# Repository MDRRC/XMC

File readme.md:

# Xpressnet Manual Control

The XpressNet Manual Control (Xmc) is manual control for the [XPressnet bus](www.lenzusa.com/1newsite1/Manuals/xpressnet.pdf) based on 

 * An [Maple Mini STM32 board](https://www.leaflabs.com/maple/) variant from China with **128K flash** memory and not the 64K variant!
 * RS485 driver IC
 * AT24C256 memory IC for storage of settings and locomotive data.
 * 128*128 pixel ST7735 LCD. When ordering a display make sure the pinning is the same as shown in image below
 * Push buttons for controlling functions / accesory decoders / menu related actions. 
 * Pulse switch for setting speed / menu related actions.
 
The user interface is nearly the same as with the WMC application and it's tried to reuse / update library's created for WMC.

## Tested with
 * [MDRRC-II](http://members.home.nl/robert.evers/mdrrc2.htm) Response ok. 
 * [Roco MultiMaus as master](https://www.roco.cc/en/product/5215-multimaus-0-0-0-0-0-004001-0/products.html) OK for locs, turnouts not tested yet.

## Schematic
The [schematic](https://github.com/MDRRC/XMC/blob/master/Doc/xmc_schematic.pdf) of the XMC.

## PCB front and back side.
The PCB from the front and back. 

## Programming the STM32 
The STM32 can be programmed without the need to build the software. By using a programming tool from the STM32 Arduino library the STM32 can be programmed with the buildin bootloader of the STM32 on the USB connection.
 * The [Stm32 Arduino library](https://github.com/rogerclarkmelbourne/Arduino_STM32) must be present on your PC.
 * Open the DOS box and enter command below (Location of files on your own PC might differ and the COM port will probably also be different, so change it accordingly!!)
 > C:/Arduino_STM32-master/tools/win/maple_upload.bat COM9 1 1EAF:0003 C:/LocationOfBinFileOnYourPc/Xmc.bin
 * The bin file is flashed into the STM32.
 * When ready, the screen stays gray for ~3 seconds and subsequent the start screen appears.
 
## Programming the STM32 with FLASHER-STM32
The STM32 can also be programmed with [Flasher-STM32](https://www.st.com/en/development-tools/flasher-stm32.html)
 * Connect an USB serial to TTL level (!) adapter to RX1 and TX1 (pin 25 and 26). The USB connector can NOT be used in this case for programmming!!! 
 * Connect the BOOT1 pin to ground when programming the STM32 out out the XMC PCB. 
 * Connect an USB cable to the USB connector of the STM32 module so it has supply voltage when programming the STM32 out out the XMC PCB. 
 * Follow instructions of chapter 5. Software update of [MDRRC-II Lite](https://github.com/MDRRC/Doc/blob/master/mdrrc_ii_lite.zip)
 * Select the XmcComplete.bin and flash the file. The bin file is WITH bootloader! 
 * When ready press RESet button, the screen stays gray for ~3 seconds and subsequent the start screen appears.   
 
## Used library's
If you want to build the code yourself or update / change the code following library's are required.
 * [XmcApp](https://github.com/MDRRC/XmcApp) the main state machine of the application.
 * [TinyFsm](https://github.com/digint/tinyfsm) for state machine framework.
 * [XpressNet](https://github.com/MDRRC/XpressNet) for XpressNet protocol.
 * [Bounce2](https://github.com/thomasfredericks/Bounce2) for debouncing switches.
Bounce requires an update for use in the XMC application, add the include and replace the attach function with code below
```c
#include "app_cfg.h"
 
void Bounce::attach(int pin, int mode)
{
  #ifdef MCU_STM32F103RB
  pinMode(pin, (WiringPinMode)(mode));
  #else
  pinMode(pin, mode);
  #endif
  this->attach(pin);
}
```
 * [Adafruit-ST7735-Library](https://github.com/adafruit/Adafruit-ST7735-Library) to control the display.
 * [WmcTft](https://github.com/MDRRC/WmcTft) for graphics within the XMC application.
 * [Adafruit-GFX-Library](https://github.com/adafruit/Adafruit-GFX-Library) for graphic control of the display.
 * [LocLib](https://github.com/MDRRC/LocLib) for handling locomotive data within the XMC application.
 * [WmcCv](https://github.com/MDRRC/WmcCv) for changing CV's.
 * [WmcCli](https://github.com/MDRRC/WmcCli) for the command line interface over the USB serial port.
 * [Stm32 Arduino library](https://github.com/rogerclarkmelbourne/Arduino_STM32), use the [1.0.0 release](https://github.com/rogerclarkmelbourne/Arduino_STM32/releases/tag/v1.0.0)! The most recent version at the master may give problems because of some changes.  
 
 In the Stm32 Arduino library
 * Remove or rename (.x for example) ..\Arduino_STM32-master\STM32F1\cores\maple\libmaple\usart.c so it's NOT build
 * Remove or rename (.x for example) ..\Arduino_STM32-master\STM32F1\cores\maple\libmaple\usart_f1.c so it's NOT build 
 * Remove or rename (.x for example) ..\Arduino_STM32-master\STM32F1\system\libmaple\usart_private.h so it's NOT build 
 
 The three files are in [XpressNet](https://github.com/MDRRC/XpressNet) and are required for correct handling of 9 bit communication handling.

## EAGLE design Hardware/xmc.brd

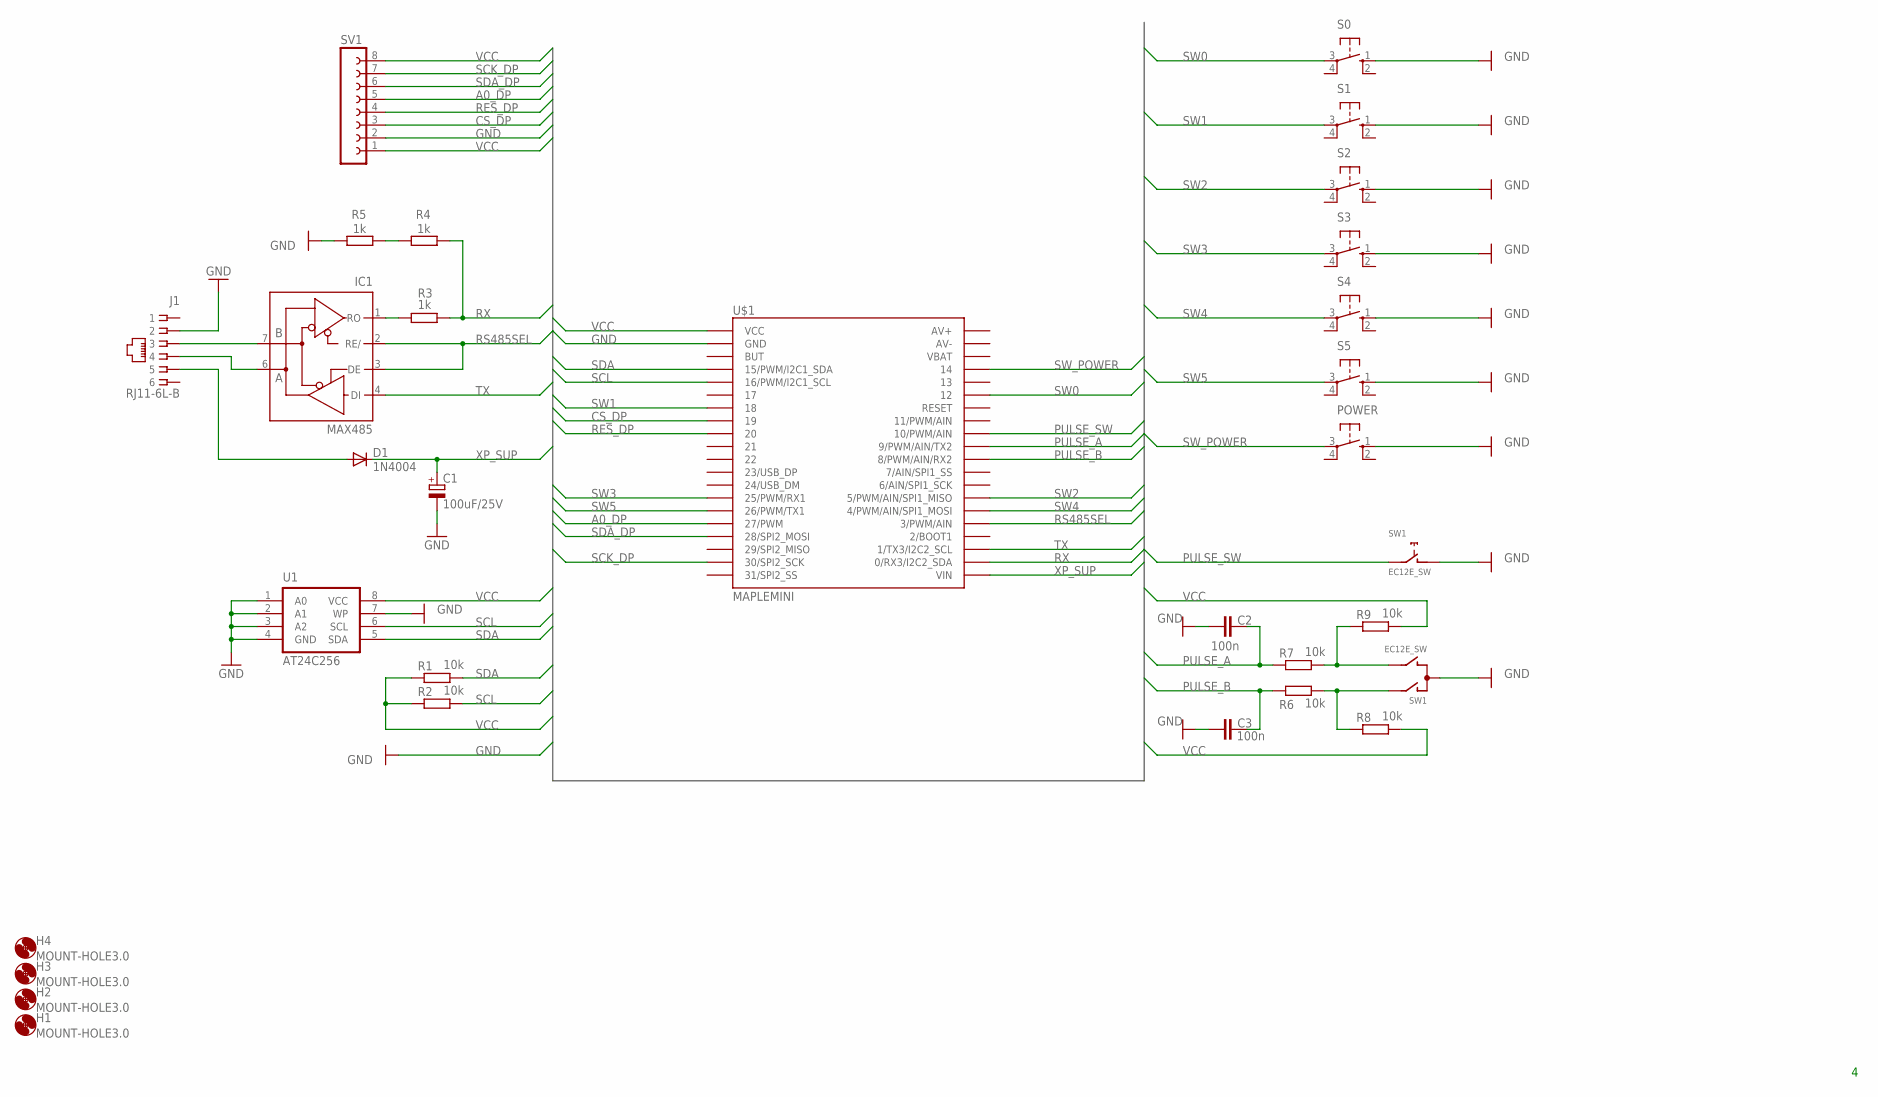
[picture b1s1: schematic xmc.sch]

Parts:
C1: 100uF/25V; E2,5-6
C2, C3: 100n; C025-024X044
D1: 1N4004; DO41-10
H1, H2, H3, H4: MOUNT-HOLE3.0; 3,0
IC1: MAX485; SO08
J1: RJ11-6L-B; RJ11-NO_SHIELD
POWER: 10-XX; B3F-10XX
R1, R2, R6, R7, R8, R9: 10k; 0207/7
R3, R4, R5: 1k; 0207/7
S0, S1, S2, S3, S4, S5: 10-XX; B3F-10XX
SV1: FE08-1; FE08
SW1: EC12E_SW; ALPS_EC12E_SW
U1: AT24C256; SO08-8S1
U$1: MAPLEMINI; 20-DIP

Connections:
A0_DP: SV1.5, U$1.16 (27/PWM)
CS_DP: SV1.3, U$1.8 (19)
GND: C1.-, C2.2, C3.2, IC1.5 (GND), J1.2, POWER.1 (S), R5.2, S0.1 (S), S1.1 (S), S2.1 (S), S3.1 (S), S4.1 (S), S5.1 (S), SV1.2, SW1.C, SW1.D (1), U1.1 (A0), U1.2 (A1), U1.3 (A2), U1.4 (GND), U1.7 (WP), U$1.2 (GND)
unnamed: R7.2, R9.1, SW1.B
unnamed: R6.2, R8.1, SW1.A
unnamed: D1.A, J1.5
unnamed: IC1.1 (RO), R3.1
unnamed: R4.2, R5.1
unnamed: IC1.7 (B), J1.3
unnamed: IC1.6 (A), J1.4
PULSE_A: C2.1, R7.1, U$1.31 (9/PWM/AIN/TX2)
PULSE_B: C3.1, R6.1, U$1.30 (8/PWM/AIN/RX2)
PULSE_SW: SW1.E (2), U$1.32 (10/PWM/AIN)
RES_DP: SV1.4, U$1.9 (20)
RS485SEL: IC1.2 (RE/), IC1.3 (DE), U$1.25 (3/PWM/AIN)
RX: R3.2, R4.1, U$1.22 (0/RX3/I2C2_SDA)
SCK_DP: SV1.7, U$1.19 (30/SPI2_SCK)
SCL: R2.2, U1.6 (SCL), U$1.5 (16/PWM/I2C1_SCL)
SDA: R1.2, U1.5 (SDA), U$1.4 (15/PWM/I2C1_SDA)
SDA_DP: SV1.6, U$1.17 (28/SPI2_MOSI)
SW0: S0.3, U$1.35 (12)
SW1: S1.3, U$1.7 (18)
SW2: S2.3, U$1.27 (5/PWM/AIN/SPI1_MISO)
SW3: S3.3, U$1.14 (25/PWM/RX1)
SW4: S4.3, U$1.26 (4/PWM/AIN/SPI1_MOSI)
SW5: S5.3, U$1.15 (26/PWM/TX1)
SW_POWER: POWER.3, U$1.37 (14)
TX: IC1.4 (DI), U$1.23 (1/TX3/I2C2_SCL)
VCC: IC1.8 (VCC), R1.1, R2.1, R8.2, R9.2, SV1.1, SV1.8, U1.8 (VCC), U$1.1 (VCC)
XP_SUP: C1.+, D1.C, U$1.21 (VIN)

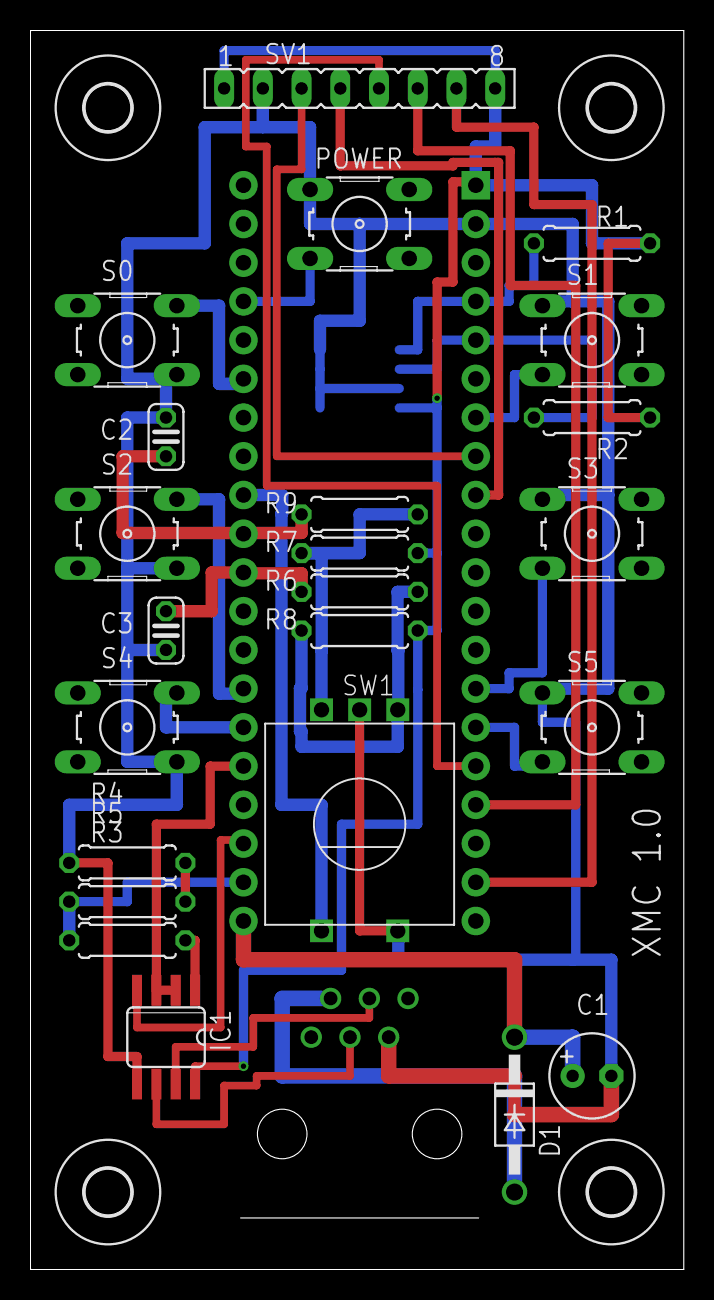
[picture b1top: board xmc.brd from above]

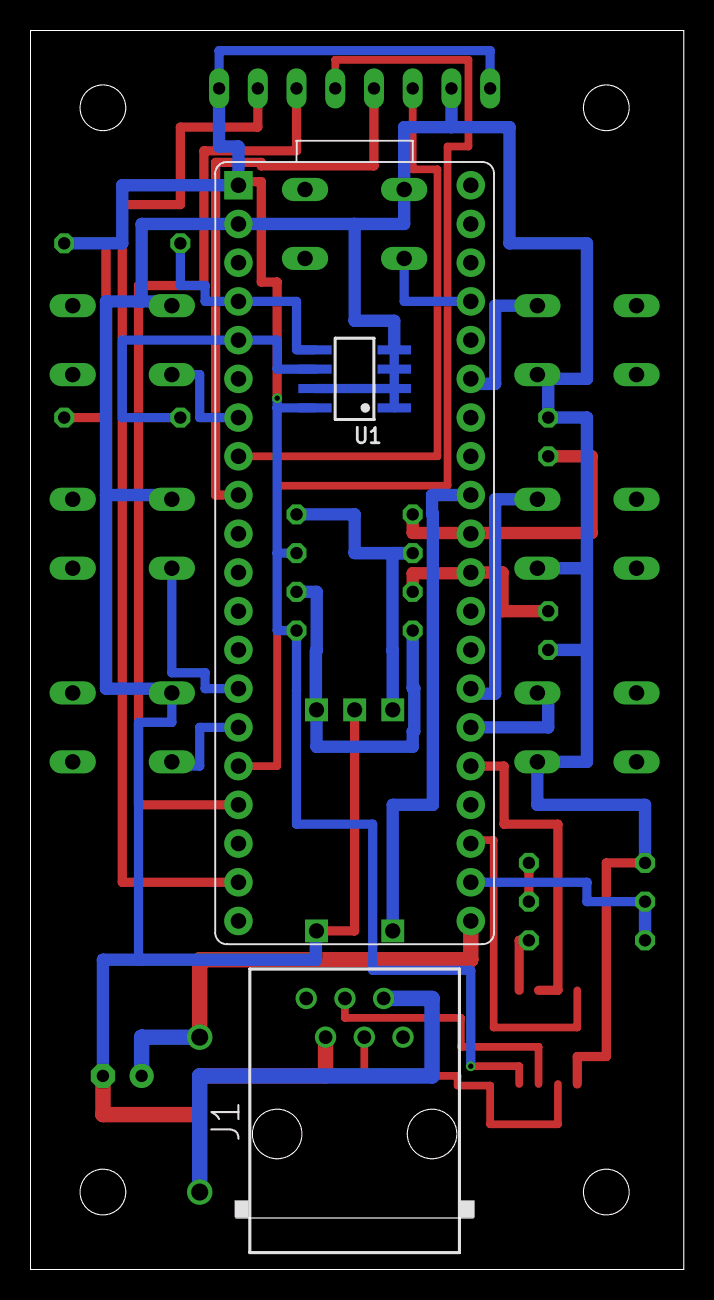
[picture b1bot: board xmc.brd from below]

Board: 2 copper layers, 42.8 x 81.3 mm, 30 parts (3 on the bottom side), 30 nets.

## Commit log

2018-06-27 Added XMC main application file.
2018-06-27 Added comments.
2018-06-28 Added file.
2018-06-30 Added picture of test setup.
2018-06-30 Picture added.
2018-06-30 Picture linbk updated.
2018-06-30 SOme textual changes.
2018-06-30 Typo...
2018-06-30 Updated text.
2018-07-02 Updated.
2018-07-02 Updated file.
2018-07-02 Initial schematic.
2018-07-02 Added directory.
2018-07-02 Links updated.
2018-07-09 Hard coded timer values replaced with defines.
2018-07-11 Button names updated, a button can have a user defined function, so F removed of name. F0 would indicate Function 0, but button 0 can have other assigned functions.
2018-07-11 Schematic updated.
2018-07-12 Button assignment to MapleMini pins changed for easier PCB design, the Maple Mini is located on the backside of the PCB.
2018-07-14 Updated button inputs to schematic version 3.
2018-08-04 Added PCB examples.
2018-08-04 Images updated.
2018-08-04 Text updated.
2018-08-04 Test updated.
2018-08-05 Added bin file.
2018-08-05 Version 1.0.0 bin file updated.
2018-08-06 Programming of STM32 added.
2018-08-06 Updating text for programming.
2018-08-06 Text programming updated.
2018-08-06 Programming text updated.
2018-08-06 Comment added at programming.
2018-08-06 Added picture.
2018-08-06 XMC and Roco MM example picture added.
2018-08-27 Version 1.1.0.
2018-08-29 Bin file version 1.01.01.
2018-08-29 Bin file version 1.01.01 with reset of AC option.
2018-09-02 Bin file with emergency stop option.
2018-09-17 Schematic C1 added value and IC1 type corrected.
2018-09-23 Enlarged component overview added.
2018-09-23 Moved file.
2019-01-21 Bin file for version 1.02.02 added (enabled POM programming).
2019-01-30 Bin file updated.
2019-02-21 Added bin file of version 01.02.04.
2019-02-21 Link added.
2019-04-10 Updated bin file to version 1.2.5.
2019-06-12 Version 1.02.05.
2019-06-23 Version 02.00.00. Names can be added to locs, also some updates in command line interface commands.
2019-06-23 Picture updated and some typo's.
2019-06-27 Version 2.00.01. Locomotive names received from a Xpressnet master like MRCC-II(-Lite) or the Roco Multimaus are now stored in the memory.
2019-09-29 Tesxt update.
2019-10-30 Version 2.00.02.
2020-03-10 Flashing updated.
2020-03-16 RX and TX pin for STM Flasher added.
2020-06-03 Added handling of two serial (uart) related files.
2020-06-03 Trying to get bullet points correct.
2020-06-03 Removed text.
2020-06-04 Version 2.1.0 with storage of last selected loc.
2020-06-11 Flashing added text when STM module is programmed out the XMC PCB and rename example added.
2020-06-14 Added complete image of XMC (including maple_nini_boot20.bin) from https://github.com/rogerclarkmelbourne/STM32duino-bootloader
2020-08-08 Added picture of backside display.
2020-08-08 Link to foto backside display for pinning added.
2020-08-08 Text update.
2020-09-09 Updated description regarding the XPressNet library.
2020-10-04 Maple Mini use the 128K Flash variant and not the 64K variant.
2020-10-18 Version 2.1.1
    * Direction change corrected.
    * When deleting show delete during deleting.
    * Changing functions updates so new functions are displayed when going back to normal control.
2020-11-30 Updated bin files to version 2.01.02 for the pulse invert option.
2020-12-26 Same as WMC adding faster loc selection. After push button is released while selecting locs send an release event so actual selected loc data can be retrieved.
2021-01-04 Added Eagle files.
2021-01-04 Version 2.2.0. * "faster" selection of locomotives, when selecting the loc address is set to white color. * When a selected loc is controlled by another (XPressNet) device the loc symbol is turned ye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
    Tested with MDRRC-II (lite) and Roco LocMaus and in both situations the yellow symbol is not shown when expected.. On the Roco setup only when the set speed of the other device was zero, on MDRRC-II 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
    Be aware, settings will be lost!
2021-12-31 Version 02.02.01 (change in CV mode handling).
2022-01-02 Updated complete bin file to version 02.02.01.

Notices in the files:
parts and their libraries:
memory-atmel: Copyright (C) 2008, Bob Starr
